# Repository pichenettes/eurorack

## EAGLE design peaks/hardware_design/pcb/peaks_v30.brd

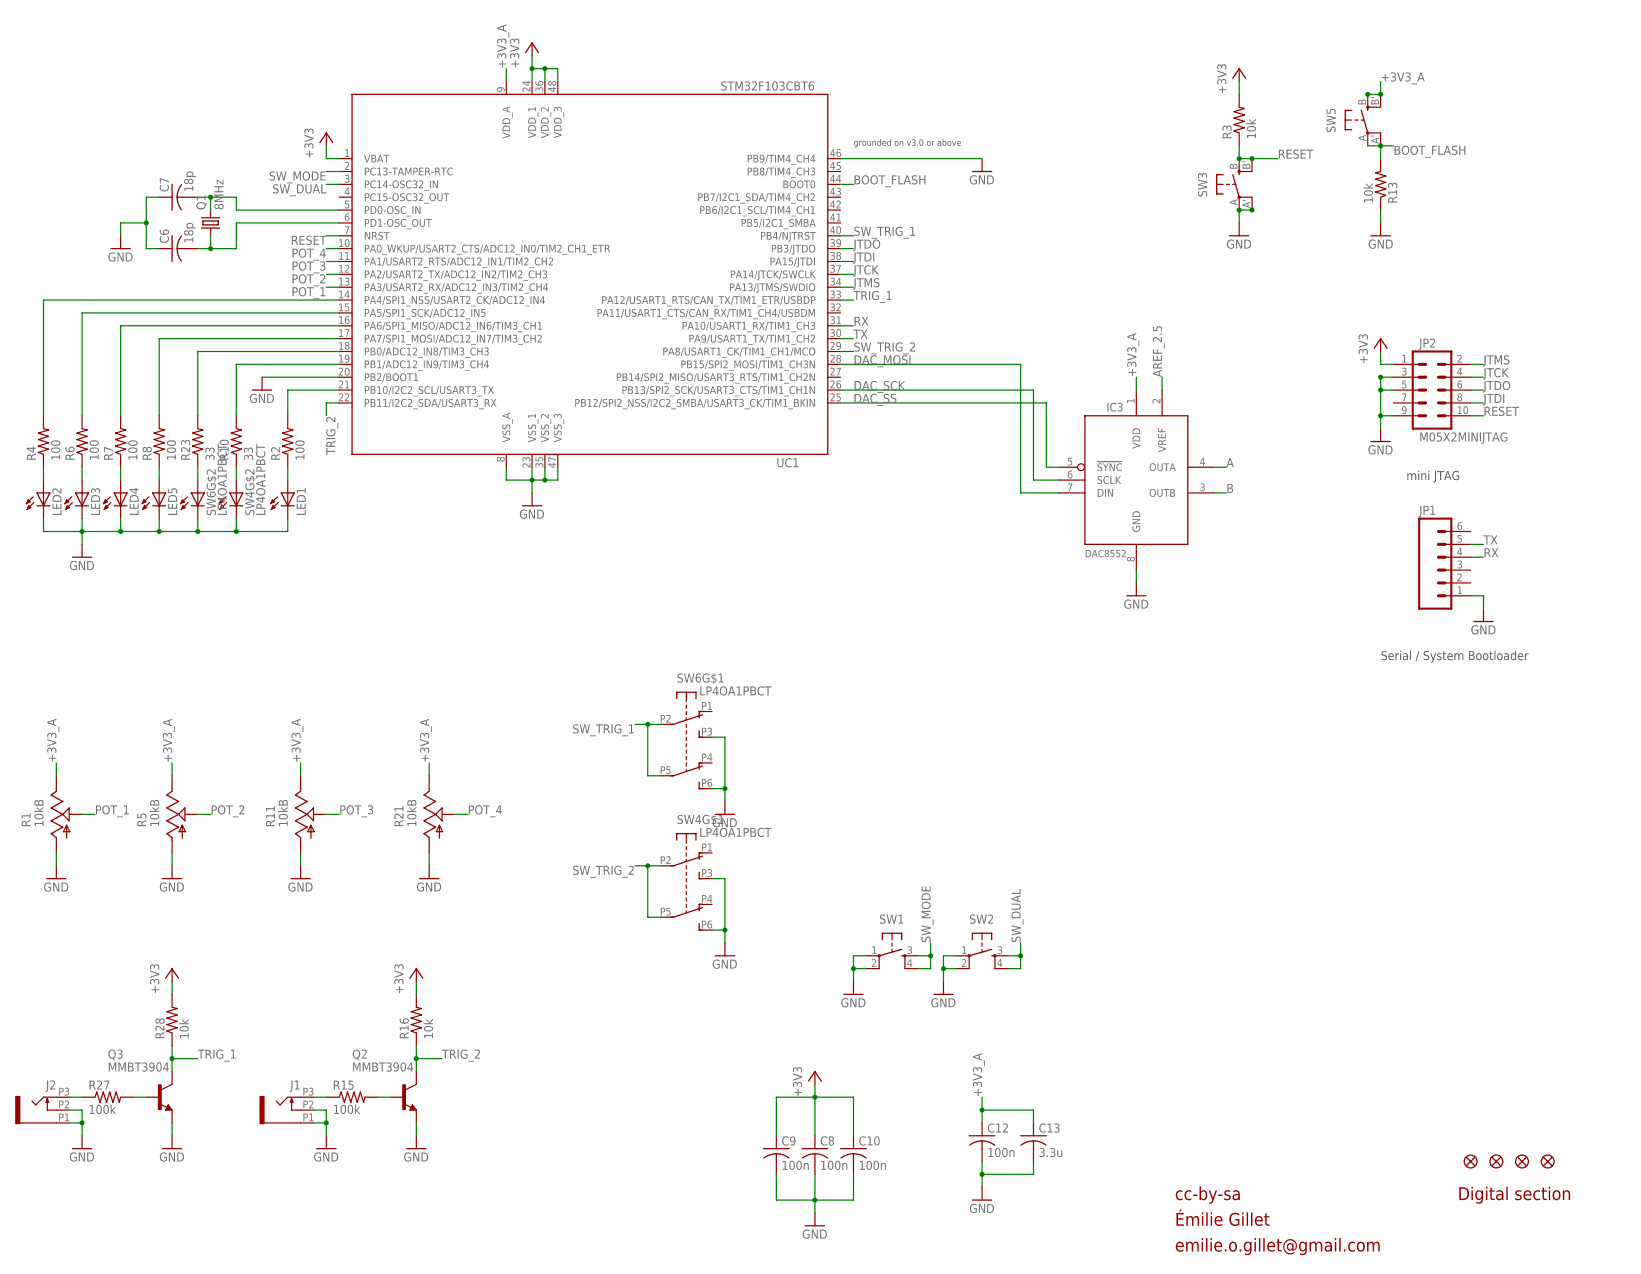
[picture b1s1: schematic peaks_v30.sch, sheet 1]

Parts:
C6, C7: 18p; C0603
C8, C9, C10, C12: 100n; C0603
C13: 3.3u; C0603
F1, F2, F3, F4: FIDUCIAL1X2; FIDUCIAL-1X2
IC3: DAC8552; MSOP-8
J1, J2: PJ301_THONKICONN6; WQP_PJ_301M6
JP1: M06SIP; 1X06
JP2: M05X2MINIJTAG; 2X5-1.27
LED1, LED2, LED3, LED4, LED5: LED3MM
Q1: 8MHz; HC49UP
Q2, Q3: MMBT3904; SOT23-BEC
R1, R5, R11, R21: 10kB; ALPS_POT_VERTICAL_PS
R2, R4, R6, R7, R8: 100; R0603
R3, R13, R16, R28: 10k; R0603
R10, R23: 33; R0603
R15, R27: 100k; R0603
SW1, SW2: TAC_SWITCHPTH; TACTILE-PTH
SW3, SW5: EVQQ2; EVQ-Q2
SW4, SW6: LP4OA1PBCT
UC1: STM32F103CBT6; LQFP48

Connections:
+3V3: C8.1, C9.1, C10.1, JP2.1, R3.2, R16.2, R28.2, UC1.1 (VBAT), UC1.24 (VDD_1), UC1.36 (VDD_2), UC1.48 (VDD_3); also elsewhere on the board
+3V3_A: C12.1, C13.1, IC3.1 (VDD), R1.P$1 (E), R5.P$1 (E), R11.P$1 (E), R21.P$1 (E), SW5.B (S), SW5.B' (S1), UC1.9 (VDD_A); also elsewhere on the board
A: IC3.4 (OUTA); also elsewhere on the board
AREF_2.5: IC3.2 (VREF); also elsewhere on the board
B: IC3.3 (OUTB); also elsewhere on the board
BOOT_FLASH: R13.2, SW5.A, SW5.A' (P1), UC1.44 (BOOT0)
DAC_MOSI: IC3.7 (DIN), UC1.28 (PB15/SPI2_MOSI/TIM1_CH3N)
DAC_SCK: IC3.6 (SCLK), UC1.26 (PB13/SPI2_SCK/USART3_CTS/TIM1_CH1N)
DAC_SS: IC3.5 (!SYNC), UC1.25 (PB12/SPI2_NSS/I2C2_SMBA/USART3_CK/TIM1_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)
GND: C6.1, C7.1, C8.2, C9.2, C10.2, C12.2, C13.2, IC3.8 (GND), J1.P1 (1), J1.P2 (2), J2.P1 (1), J2.P2 (2), JP1.1, JP2.3, JP2.5, JP2.9, LED1.K (C), LED2.K (C), LED3.K (C), LED4.K (C), LED5.K (C), Q2.E, Q3.E, R1.P$3 (A), R5.P$3 (A), R11.P$3 (A), R13.1, R21.P$3 (A), SW1.1, SW1.2, SW2.1, SW2.2, SW3.A, SW3.A' (P1), SW4.L2, SW4.P3 (A3), SW4.P6 (B3), SW6.L2, SW6.P3 (A3), SW6.P6 (B3), UC1.8 (VSS_A), UC1.20 (PB2/BOOT1), UC1.23 (VSS_1), UC1.35 (VSS_2), UC1.46 (PB9/TIM4_CH4), UC1.47 (VSS_3); also elsewhere on the board
JTCK: JP2.4, UC1.37 (PA14/JTCK/SWCLK)
JTDI: JP2.8, UC1.38 (PA15/JTDI)
JTDO: JP2.6, UC1.39 (PB3/JTDO)
JTMS: JP2.2, UC1.34 (PA13/JTMS/SWDIO)
unnamed: J1.P3 (3), R15.1
unnamed: R23.2, UC1.18 (PB0/ADC12_IN8/TIM3_CH3)
unnamed: LED2.A, R4.1
unnamed: LED3.A, R6.1
unnamed: LED4.A, R7.1
unnamed: LED5.A, R8.1
unnamed: C7.2, Q1.2, UC1.5 (PD0-OSC_IN)
unnamed: C6.2, Q1.1, UC1.6 (PD1-OSC_OUT)
unnamed: R10.2, UC1.19 (PB1/ADC12_IN9/TIM3_CH4)
unnamed: R4.2, UC1.14 (PA4/SPI1_NSS/USART2_CK/ADC12_IN4)
unnamed: R6.2, UC1.15 (PA5/SPI1_SCK/ADC12_IN5)
unnamed: R7.2, UC1.16 (PA6/SPI1_MISO/ADC12_IN6/TIM3_CH1)
unnamed: R8.2, UC1.17 (PA7/SPI1_MOSI/ADC12_IN7/TIM3_CH2)
unnamed: Q2.B, R15.2
unnamed: R23.1, SW6.L1
unnamed: R10.1, SW4.L1
unnamed: LED1.A, R2.1
unnamed: R2.2, UC1.21 (PB10/I2C2_SCL/USART3_TX)
unnamed: J2.P3 (3), R27.1
unnamed: Q3.B, R27.2
POT_1: R1.P$2 (S), UC1.13 (PA3/USART2_RX/ADC12_IN3/TIM2_CH4)
POT_2: R5.P$2 (S), UC1.12 (PA2/USART2_TX/ADC12_IN2/TIM2_CH3)
POT_3: R11.P$2 (S), UC1.11 (PA1/USART2_RTS/ADC12_IN1/TIM2_CH2)
POT_4: R21.P$2 (S), UC1.10 (PA0_WKUP/USART2_CTS/ADC12_IN0/TIM2_CH1_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)
RESET: JP2.10, R3.1, SW3.B (S), SW3.B' (S1), UC1.7 (NRST)
RX: JP1.4, UC1.31 (PA10/USART1_RX/TIM1_CH3)
SW_DUAL: SW2.3, SW2.4, UC1.3 (PC14-OSC32_IN)
SW_MODE: SW1.3, SW1.4, UC1.2 (PC13-TAMPER-RTC)
SW_TRIG_1: SW6.P2 (A2), SW6.P5 (B2), UC1.40 (PB4/NJTRST)
SW_TRIG_2: SW4.P2 (A2), SW4.P5 (B2), UC1.29 (PA8/USART1_CK/TIM1_CH1/MCO)
TRIG_1: Q3.C, R28.1, UC1.33 (PA12/USART1_RTS/CAN_TX/TIM1_ETR/USBDP)
TRIG_2: Q2.C, R16.1, UC1.22 (PB11/I2C2_SDA/USART3_RX)
TX: JP1.5, UC1.30 (PA9/USART1_TX/TIM1_CH2)

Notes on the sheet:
cc-by-sa
Digital section
mini JTAG
Serial / System Bootloader
grounded on v3.0 or above
Émilie Gillet
emilie.o.gillet@gmail.com

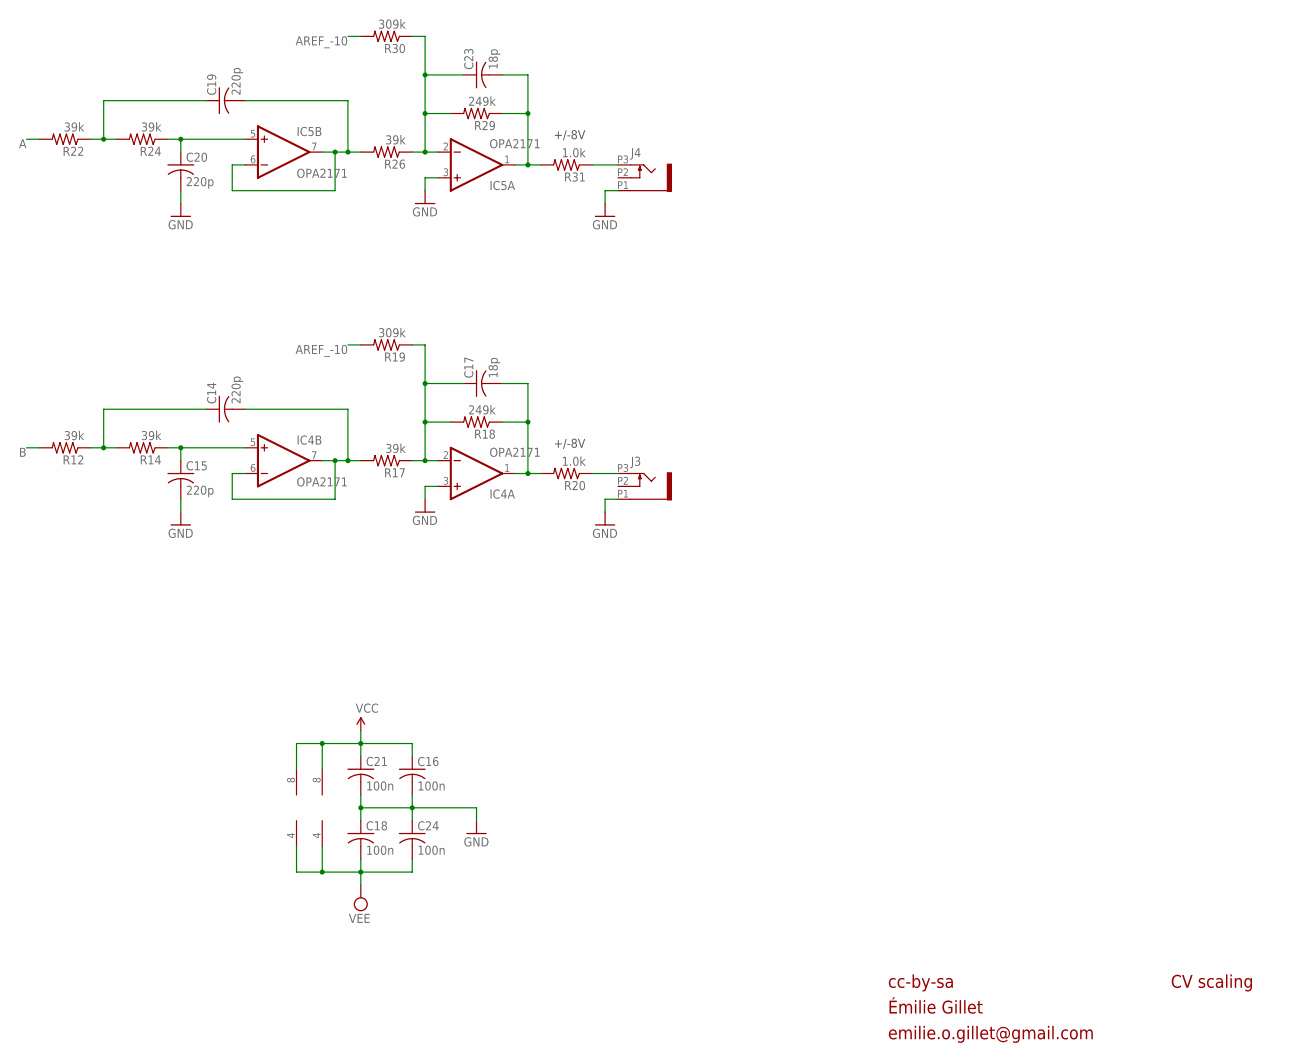
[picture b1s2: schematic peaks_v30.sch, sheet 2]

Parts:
C14, C15, C19, C20: 220p; C0603
C16, C18, C21, C24: 100n; C0603
C17, C23: 18p; C0603
IC4, IC5: OPA2171; SO08
J3, J4: PJ301_THONKICONN6; WQP_PJ_301M6
R12, R14, R17, R22, R24, R26: 39k; R0603
R18, R29: 249k; R0603
R19, R30: 309k; R0603
R20, R31: 1.0k; R0603

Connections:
A: R22.2; also elsewhere on the board
AREF_-10: R19.2, R30.2; also elsewhere on the board
B: R12.2; also elsewhere on the board
BI_OUT: C17.2, IC4.1 (OUT), R18.1, R20.2
BI_OUT1: C23.2, IC5.1 (OUT), R29.1, R31.2
F_CV: C17.1, IC4.2 (-IN), R17.1, R18.2, R19.1
F_CV1: C23.1, IC5.2 (-IN), R26.1, R29.2, R30.1
GND: C15.2, C16.2, C18.1, C20.2, C21.2, C24.1, IC4.3 (+IN), IC5.3 (+IN), J3.P1 (1), J4.P1 (1); also elsewhere on the board
unnamed: C19.2, IC5.6 (-IN), IC5.7 (OUT), R26.2
unnamed: C20.1, IC5.5 (+IN), R24.1
unnamed: C19.1, R22.1, R24.2
unnamed: J3.P3 (3), R20.1
unnamed: J4.P3 (3), R31.1
unnamed: C14.2, IC4.6 (-IN), IC4.7 (OUT), R17.2
unnamed: C15.1, IC4.5 (+IN), R14.1
unnamed: C14.1, R12.1, R14.2
VCC: C16.1, C21.1, IC4.8 (V+), IC5.8 (V+); also elsewhere on the board
VEE: C18.2, C24.2, IC4.4 (V-), IC5.4 (V-); also elsewhere on the board

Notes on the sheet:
+/-8V
cc-by-sa
CV scaling
Émilie Gillet
emilie.o.gillet@gmail.com

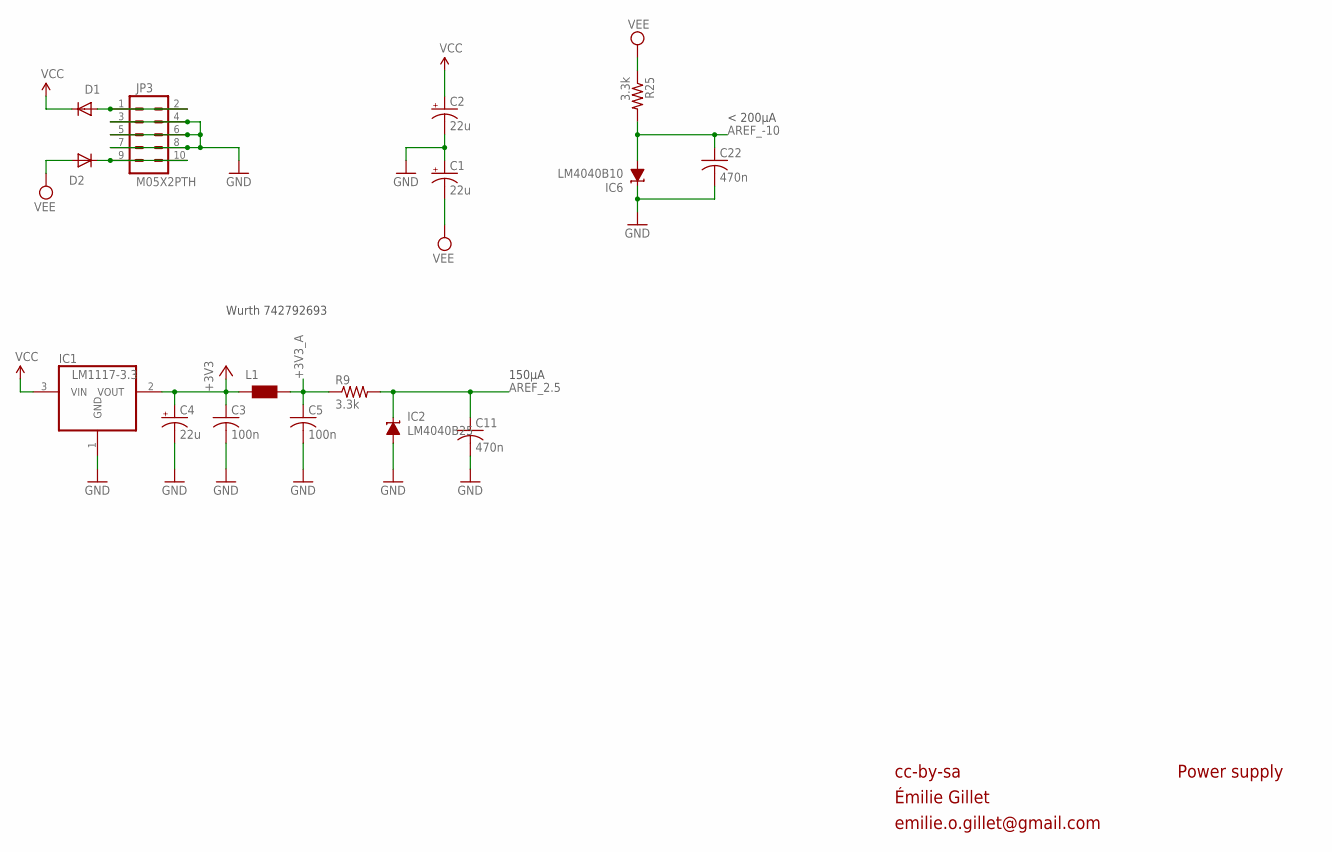
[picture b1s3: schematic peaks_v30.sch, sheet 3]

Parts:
C1, C2, C4: 22u; PANASONIC_C
C3, C5: 100n; C0603
C11, C22: 470n; C0603
D1, D2: 1N5819HW; SOD123
IC1: LM1117-3.3; SOT223
IC2: LM4040B25; DBZ_R-PDSO-G3
IC6: LM4040B10; DBZ_R-PDSO-G3
JP3: M05X2PTH; AVR_ICSP
L1: WE-CBF_0603; 0603
R9, R25: 3.3k; R0603

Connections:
+3V3: C3.1, C4.+, IC1.2 (VOUT), L1.1; also elsewhere on the board
+3V3_A: C5.1, L1.2, R9.1; also elsewhere on the board
AREF_2.5: C11.1, IC2.1 (C), R9.2; also elsewhere on the board
AREF_-10: C22.1, IC6.2 (A), R25.2; also elsewhere on the board
GND: C1.+, C2.-, C3.2, C4.-, C5.2, C11.2, C22.2, IC1.1 (GND), IC2.2 (A), IC6.1 (C), JP3.3, JP3.4, JP3.5, JP3.6, JP3.7, JP3.8; also elsewhere on the board
unnamed: D1.A, JP3.1, JP3.2
unnamed: D2.C, JP3.9, JP3.10
VCC: C2.+, D1.C, IC1.3 (VIN); also elsewhere on the board
VEE: C1.-, D2.A, R25.1; also elsewhere on the board

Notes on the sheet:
cc-by-sa
Power supply
Wurth 742792693
< 200µA
150µA
Émilie Gillet
emilie.o.gillet@gmail.com

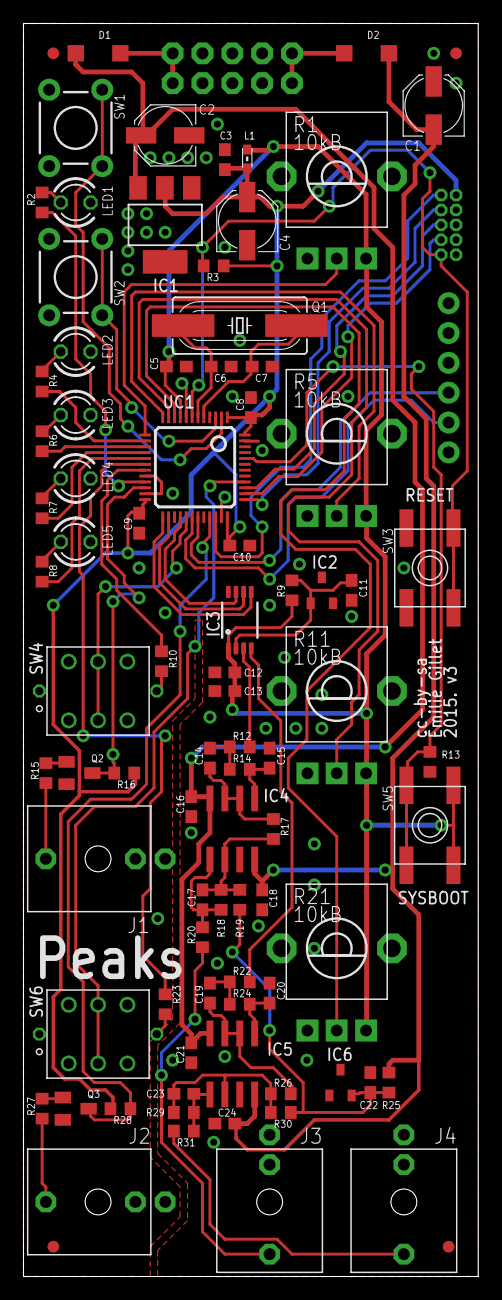
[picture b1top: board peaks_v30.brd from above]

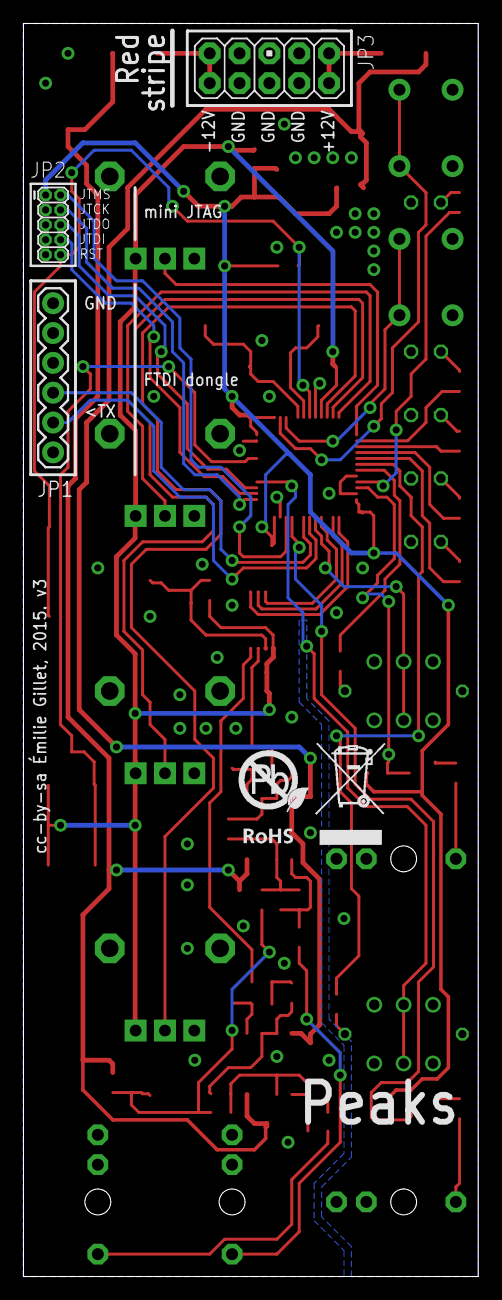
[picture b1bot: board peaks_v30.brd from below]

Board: 2 copper layers, 38.7 x 106.7 mm, 91 parts (4 on the bottom side), 64 nets.

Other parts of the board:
U$2: ROHS

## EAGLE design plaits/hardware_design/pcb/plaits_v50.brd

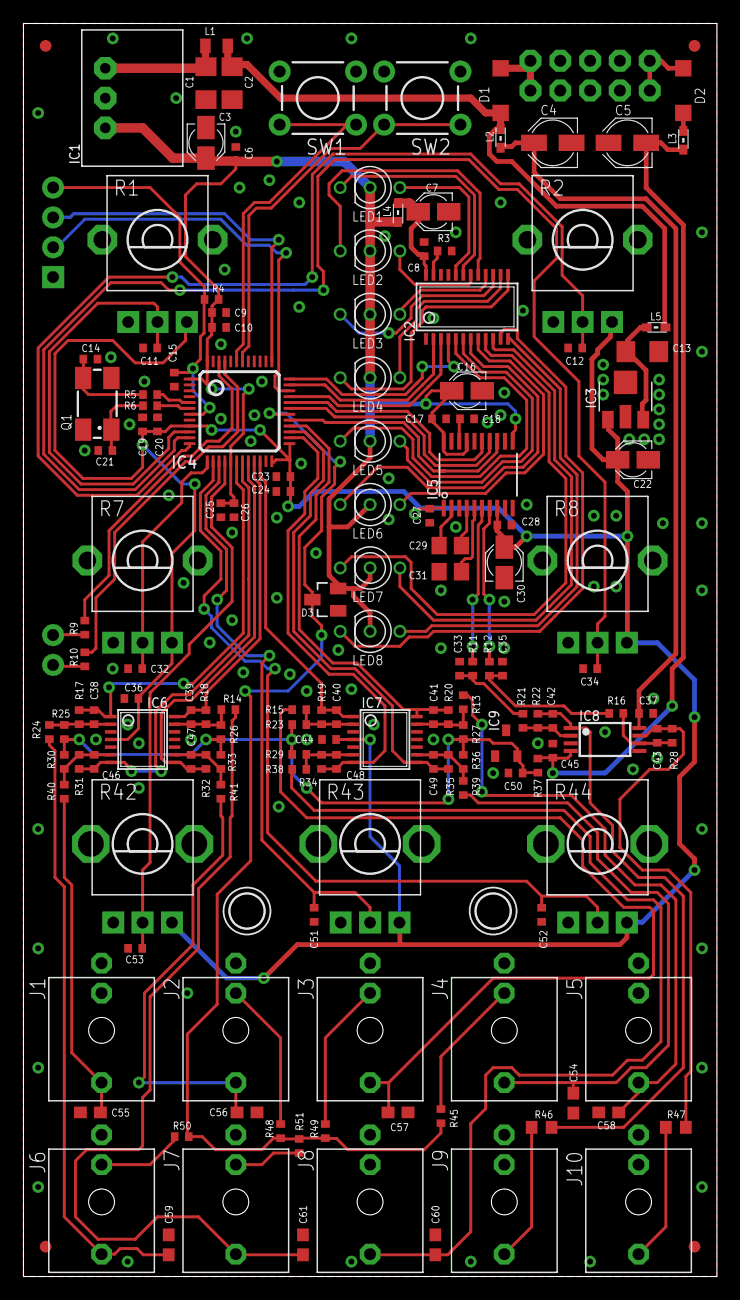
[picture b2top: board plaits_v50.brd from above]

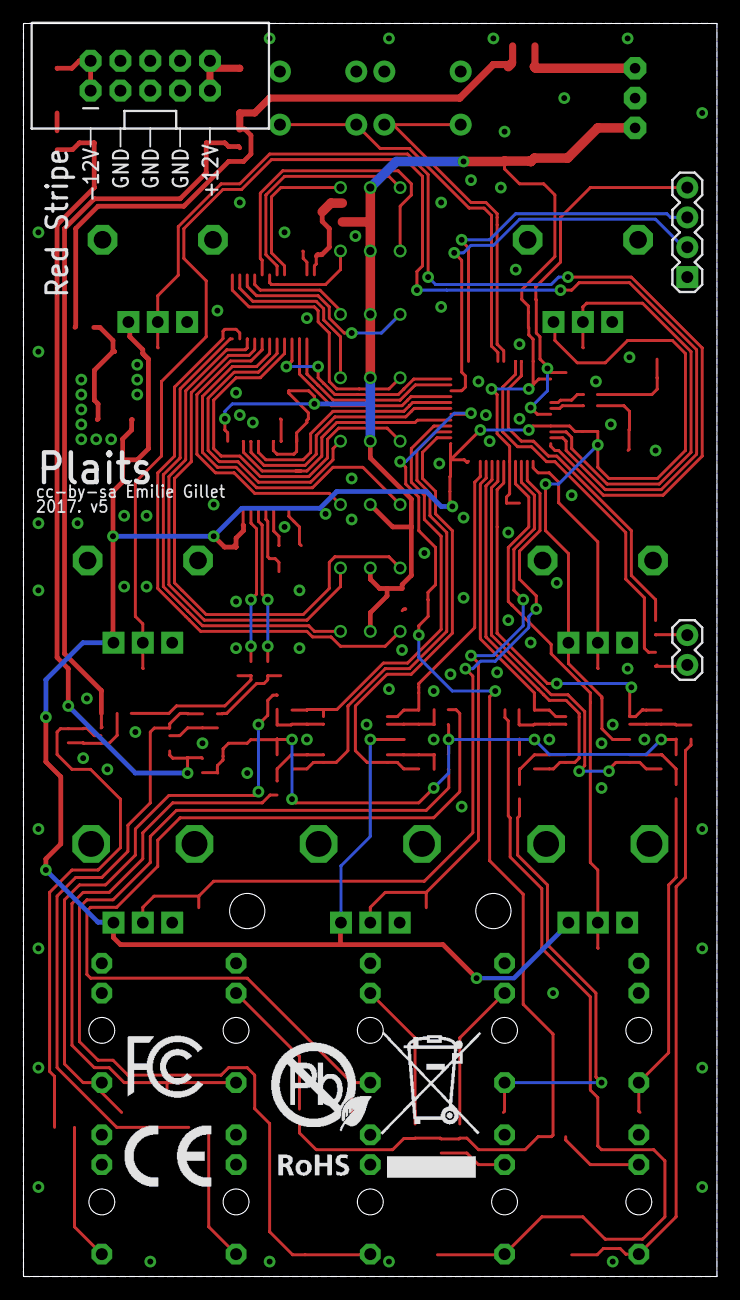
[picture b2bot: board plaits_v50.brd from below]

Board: 2 copper layers, 59.0 x 106.7 mm, 162 parts (6 on the bottom side), 100 nets.

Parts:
C1, C2, C13: 22u; C1206
C3, C7, C16, C22, C30: 10u; PANASONIC_A
C4, C5: 22u; PANASONIC_B
C6, C8, C10, C11, C12, C15, C17, C18, C20, C23, C26, C27, C28, C32, C34, C36, C37, C44, C45, C51, C52, C53: 100n; C0402
C9, C19, C24, C25, C50: 1u; C0402
C14, C21: 20p; C0402
C29, C31: 2.2u; C0805
C33, C35, C39, C40, C41, C47, C48, C49: 1.0n; C0402
C38, C42, C43, C46: 100p; C0402
C54, C55, C56, C57, C58, C59, C60, C61: ESD; C0603
D1, D2: 1N5819HW; SOD123
D3: BAT54S; SOT23
H2, H3: MOUNT-HOLE; 3,0TINY
IC1: R-78E3.3-0.5; WE78
IC2: TLC59281DBQ; TSSOP24_0635
IC3: LD2981ABU33; SOT89
IC4: STM32F373CCT6; LQFP48
IC5: PCM5100APW; SSOP20
IC6, IC7: MCP6004; TSSOP14_065
IC8: TL072PW; TSSOP08
IC9: LM4040B10; DBZ_R-PDSO-G3
J1, J2, J3, J4, J5, J6, J7, J8, J9, J10: PJ301_THONKICONN6; WQP_PJ_301M6
JP1, JP2, JP3, JP4: FIDUCIAL1X2; FIDUCIAL-1X2
JP5: 1X02
JP6: 1X04
JP8: M05X2SHD; 2X5-SHROUDED
L1: 33u; L2012C
L2, L3, L4, L5: 0603
LED1, LED2, LED3, LED4, LED5, LED6, LED7, LED8: SSL-LX3059IGW-CA; LED-BICOLOR-THROUGHHOLE-LUMEX
Q1: 8MHz; CTS406
R1, R2, R7, R8: 10kB; ALPS_POT_VERTICAL_PS
R3, R4, R16, R21, R45, R48, R49, R50, R51: 10k; R0402
R5, R6, R9, R10: 100; R0402
R11, R12, R37: 2.2k; R0402
R13, R14, R15, R24, R38, R39, R40, R41: 100k; R0402
R17: 56k; R0402
R18, R20, R22, R28, R31, R34: 33k; R0402
R19, R32, R35: 20k; R0402
R23, R33, R36: 120k; R0402
R25, R27, R30: 200k; R0402
R26: 110k; R0402
R29: 140k; R0402
R42, R43, R44: 10kB; ALPS_POT_VERTICAL
R46, R47: 1.0k; R0603
SW1, SW2: TACTILE-PTH
U$1: FCC_MEDIUM
U$2: ROHS_BIG
U$3: CE_MEDIUM

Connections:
+3V3: C3.+, C6.1, C9.1, C10.1, C16.+, C17.1, C25.1, C26.1, D3.2, IC1.3, IC4.1, IC4.17, IC4.48, IC5.11, IC5.17, IC5.20, L4.2, LED1.A, LED2.A, LED3.A, LED4.A, LED5.A, LED6.A, LED7.A, LED8.A, R4.1
+3V3_A: C19.1, C20.1, C22.+, C23.1, C24.1, C27.1, C28.1, C30.+, C36.1, C44.1, IC3.1, IC4.9, IC4.24, IC4.25, IC5.1, IC5.8, IC6.4, IC7.4, R1.P$1, R2.P$1, R7.P$1, R8.P$1, R42.P$1, R43.P$1, R44.P$1
ADC_FM: C40.2, IC4.22, IC7.1, R19.1
ADC_GATE: C39.2, IC4.21, IC6.14, R18.1
ADC_HARMONICS: C41.2, IC4.28, IC7.14, R20.1
ADC_MODEL: C46.2, IC4.19, IC6.7, R31.1
ADC_MORPH: C49.2, IC4.27, IC7.8, R35.1
ADC_TIMBRE: C47.2, IC4.20, IC6.8, R32.1
ADC_TRIG: C38.2, IC4.18, IC6.1, R17.1
ADC_V_OCT: C48.2, IC4.26, IC7.7, R34.1
AREF_-10: C50.1, IC9.2, R23.2, R25.2, R26.2, R27.2, R29.2, R30.2, R33.2, R36.2, R37.2
DAC_BCK: IC4.29, IC5.13
DAC_DIN: IC4.31, IC5.14
DAC_LRCK: IC4.32, IC5.15
FM_IN: C57.1, J3.P3, R15.2
FREQ_ATT: C51.1, IC4.15, R43.P$2
FREQ_POT: C11.1, IC4.10, R1.P$2
GATE_IN: C61.1, J7.P3, R14.2
GATE_IN1: C59.1, J6.P3, R24.2
GND: C1.2, C2.2, C3.-, C4.-, C5.+, C6.2, C7.-, C8.2, C9.2, C10.2, C11.2, C12.2, C13.2, C14.1, C15.2, C16.-, C17.2, C18.2, C19.2, C20.2, C21.1, C22.-, C23.2, C24.2, C25.2, C26.2, C27.2, C28.2, C30.-, C31.2, C32.2, C33.2, C34.2, C35.2, C36.2, C37.2, C44.2, C45.1, C50.2, C51.2, C52.2, C53.2, C54.2, C55.2, C56.2, C57.2, C58.2, C59.2, C60.2, C61.2, D3.1, IC1.2, IC2.1, IC2.21, IC3.2, IC4.8, IC4.23, IC4.44, IC4.47, IC5.3, IC5.9, IC5.10, IC5.12, IC5.16, IC5.19, IC6.3, IC6.5, IC6.10, IC6.11, IC6.12, IC7.3, IC7.5, IC7.10, IC7.11, IC7.12, IC8.3, IC8.5, IC9.1, J1.P1, J1.P2, J2.P1, J3.P1, J4.P1, J5.P1, J5.P2, J6.P1, J7.P1, J8.P1, J8.P2, J9.P1, J10.P1, JP6.1, JP8.3, JP8.4, JP8.5, JP8.6, JP8.7, JP8.8, Q1.2, Q1.4, R1.P$3, R2.P$3, R3.2, R7.P$3, R8.P$3, R42.P$3, R43.P$3, R44.P$3, SW1.1, SW1.2, SW2.1, SW2.2
HARMONICS_IN: C58.1, J5.P3, R13.2
HARMONICS_POT: C12.1, IC4.12, R2.P$2
LEDS_SCK: IC2.3, IC4.33
LEDS_SIN: IC2.2, IC4.35
LEDS_SS: IC2.4, IC4.36
MODEL_IN: C55.1, J1.P3, R40.2
MORPH_ATT: C52.1, IC4.14, R44.P$2
MORPH_IN: C54.1, J4.P3, R39.2
MORPH_POT: C34.1, IC4.11, R8.P$2
unnamed: C1.1, IC1.1, L1.2
unnamed: IC2.12, LED8.GREEN_C
unnamed: J6.P2, R50.2
unnamed: C38.1, IC6.2, R17.2, R24.1, R25.1
unnamed: IC2.11, LED8.RED_C
unnamed: C29.1, IC5.2
unnamed: IC4.5, R5.1
unnamed: IC4.6, R6.1
unnamed: IC2.10, LED7.GREEN_C
unnamed: IC2.9, LED7.RED_C
unnamed: IC2.8, LED6.GREEN_C
unnamed: IC2.13, LED4.RED_C
unnamed: IC2.7, LED6.RED_C
unnamed: IC2.14, LED4.GREEN_C
unnamed: IC2.6, LED5.GREEN_C
unnamed: C29.2, IC5.4
unnamed: IC2.15, LED3.RED_C
unnamed: IC2.16, LED3.GREEN_C
unnamed: IC2.17, LED2.RED_C
unnamed: IC2.18, LED2.GREEN_C
unnamed: IC2.19, LED1.RED_C
unnamed: IC2.5, LED5.RED_C
unnamed: IC2.20, LED1.GREEN_C
unnamed: J3.P2, R49.1
unnamed: J2.P2, R48.1
unnamed: J4.P2, R45.1
unnamed: C7.+, C8.1, IC2.24, L4.1
unnamed: C39.1, IC6.13, R14.1, R18.2, R26.1
unnamed: C14.2, Q1.3, R5.2
unnamed: C48.1, IC7.6, R29.1, R34.2, R38.1
unnamed: C56.1, J2.P3, R41.2
unnamed: C49.1, IC7.9, R35.2, R36.1, R39.1
unnamed: JP5.2, R10.1
unnamed: C40.1, IC7.2, R15.1, R19.2, R23.1
unnamed: C21.2, Q1.1, R6.2
unnamed: J7.P2, R51.1
unnamed: C46.1, IC6.6, R30.1, R31.2, R40.1
unnamed: D2.A, L3.2
unnamed: C47.1, IC6.9, R32.2, R33.1, R41.1
unnamed: C2.1, D1.C, L1.1, L2.2, L5.2
unnamed: C41.1, IC7.13, R13.1, R20.2, R27.1
unnamed: C13.1, IC3.3, L5.1
unnamed: IC5.6, R11.2
unnamed: C33.1, R11.1, R21.2
unnamed: C35.1, R12.1, R16.2
unnamed: C31.1, IC5.5
unnamed: JP5.1, R9.1
unnamed: C18.1, IC5.18
unnamed: IC5.7, R12.2
unnamed: D1.A, JP8.9, JP8.10
unnamed: C43.1, IC8.6, R16.1, R28.2
unnamed: C43.2, IC8.7, R28.1, R47.2
unnamed: C42.1, IC8.2, R21.1, R22.2
unnamed: C42.2, IC8.1, R22.1, R46.2
unnamed: D2.C, JP8.1, JP8.2
unnamed: J9.P3, R46.1
unnamed: IC2.23, R3.1
unnamed: J10.P3, R47.1
NORMALIZATION_PROBE: D3.3, IC4.30, R45.2, R48.2, R49.2, R50.1, R51.2
RESET: C15.1, IC4.7, JP6.4, R4.2
RX: IC4.46, R9.2
SWCLK: IC4.37, JP6.3
SWDIO: IC4.34, JP6.2
SW_1: IC4.43, SW1.3, SW1.4
SW_2: IC4.42, SW2.3, SW2.4
TIMBRE_ATT: C53.1, IC4.16, R42.P$2
TIMBRE_POT: C32.1, IC4.13, R7.P$2
TX: IC4.45, R10.2
VCC: C4.+, C37.1, IC8.8, L2.1
VEE: C5.-, C45.2, IC8.4, L3.1, R37.1
V_OCT_IN: C60.1, J8.P3, R38.2

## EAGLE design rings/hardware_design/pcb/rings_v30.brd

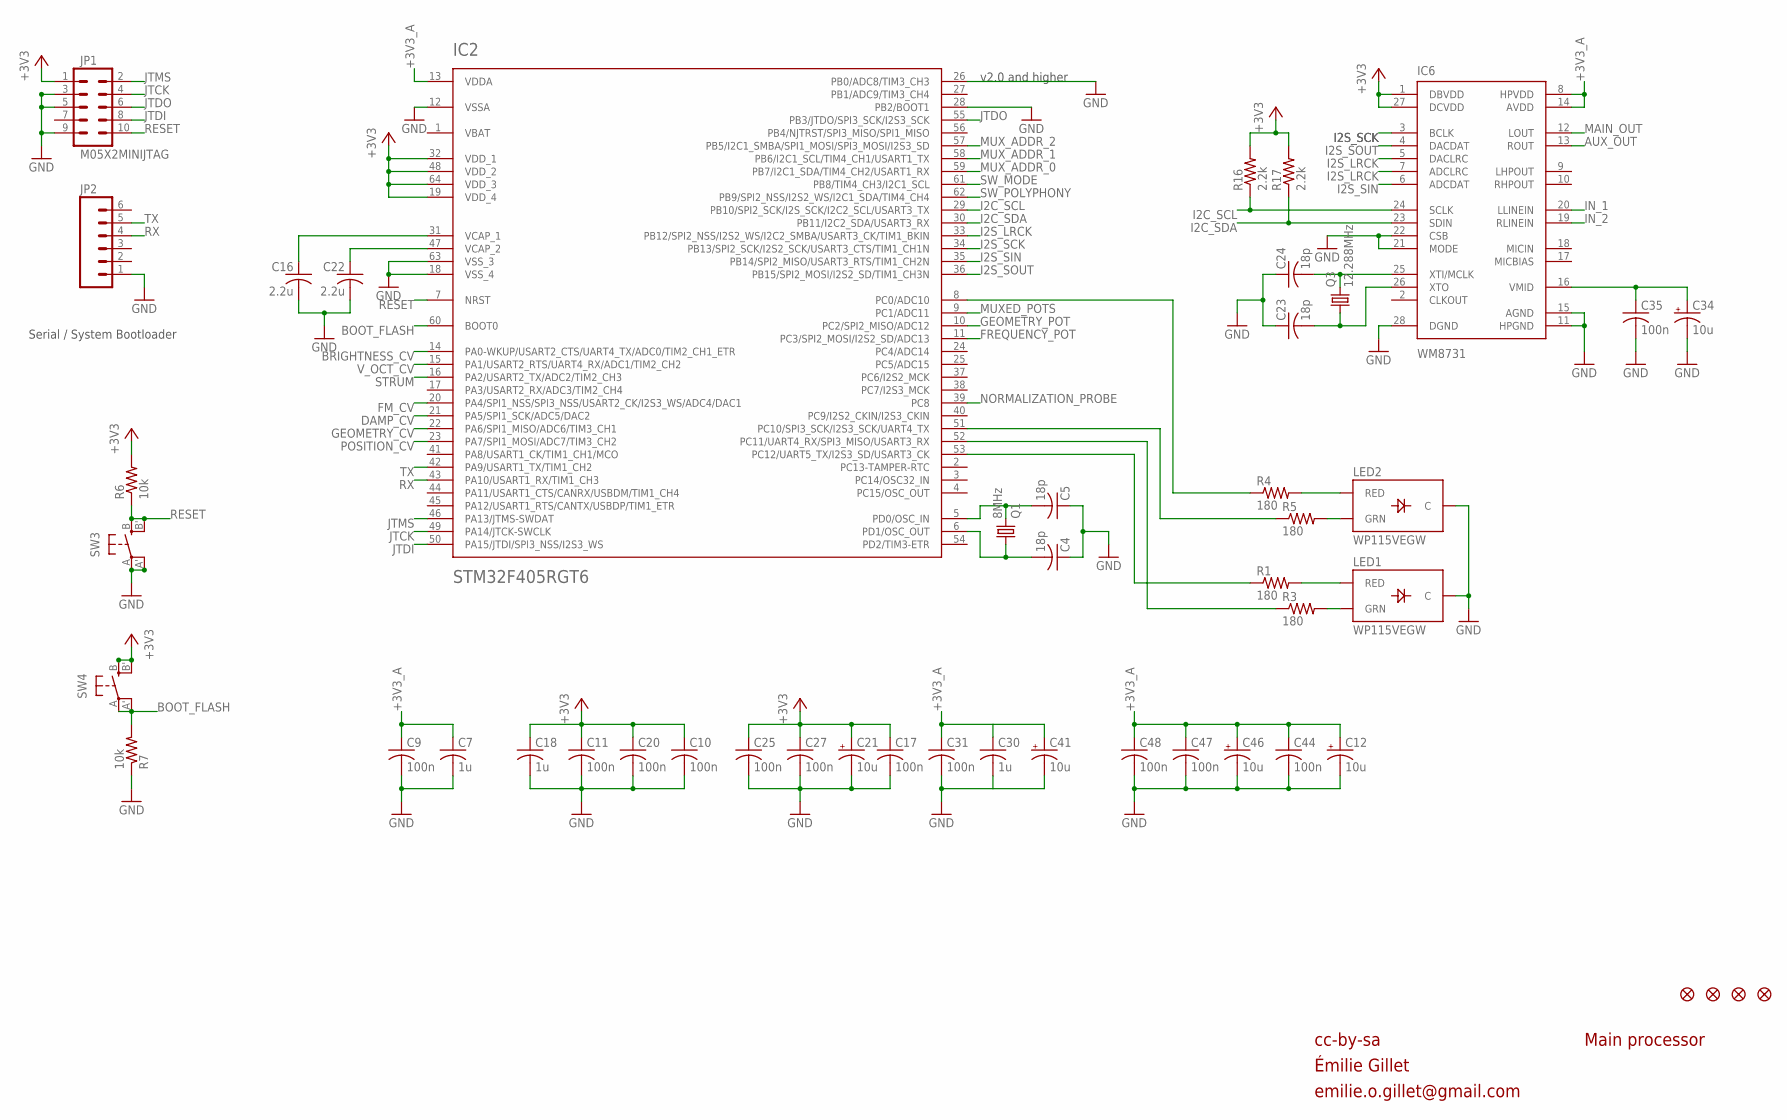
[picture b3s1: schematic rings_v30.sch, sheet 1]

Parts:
C4, C5, C23, C24: 18p; C0603
C7, C18, C30: 1u; C0603
C9, C10, C11, C17, C20, C25, C27, C31, C35, C44, C47, C48: 100n; C0603
C12, C21, C34, C41, C46: 10u; PANASONIC_A
C16, C22: 2.2u; C0805
F1, F2, F3, F4: FIDUCIAL1X2; FIDUCIAL-1X2
IC2: STM32F405RGT6; TQFP-10X10-64
IC6: WM8731; SSOP28
JP1: M05X2MINIJTAG; 2X5-1.27
JP2: M06SIP; 1X06
LED1, LED2: WP115VEGW; LED-BICOLOR-THROUGHHOLE
Q1: 8MHz; HC49UP
Q3: 12.288MHz; HC49UP
R1, R3, R4, R5: 180; R0603
R6, R7: 10k; R0603
R16, R17: 2.2k; R0603
SW3, SW4: EVQQ2; EVQ-Q2

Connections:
+3V3: C10.1, C11.1, C17.1, C18.1, C20.1, C21.+, C25.1, C27.1, IC2.19 (VDD_4), IC2.32 (VDD_1), IC2.48 (VDD_2), IC2.64 (VDD_3), IC6.1 (DBVDD), IC6.27 (DCVDD), JP1.1, R6.2, R16.2, R17.2, SW4.B (S), SW4.B' (S1); also elsewhere on the board
+3V3_A: C7.1, C9.1, C12.+, C30.1, C31.1, C41.+, C44.1, C46.+, C47.1, C48.1, IC2.13 (VDDA), IC6.8 (HPVDD), IC6.14 (AVDD); also elsewhere on the board
AUX_OUT: IC6.13 (ROUT); also elsewhere on the board
BOOT_FLASH: IC2.60 (BOOT0), R7.2, SW4.A, SW4.A' (P1)
BRIGHTNESS_CV: IC2.14 (PA0-WKUP/USART2_CTS/UART4_TX/ADC0/TIM2_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); also elsewhere on the board
DAMP_CV: IC2.21 (PA5/SPI1_SCK/ADC5/DAC2); also elsewhere on the board
FM_CV: IC2.20 (PA4/SPI1_NSS/SPI3_NSS/USART2_CK/I2S3_WS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); also elsewhere on the board
FREQUENCY_POT: IC2.11 (PC3/SPI2_MOSI/I2S2_SD/ADC13); also elsewhere on the board
GEOMETRY_CV: IC2.22 (PA6/SPI1_MISO/ADC6/TIM3_CH1); also elsewhere on the board
GEOMETRY_POT: IC2.10 (PC2/SPI2_MISO/ADC12); also elsewhere on the board
GND: C4.1, C5.1, C7.2, C9.2, C10.2, C11.2, C12.-, C16.2, C17.2, C18.2, C20.2, C21.-, C22.2, C23.1, C24.1, C25.2, C27.2, C30.2, C31.2, C34.-, C35.2, C41.-, C44.2, C46.-, C47.2, C48.2, IC2.12 (VSSA), IC2.18 (VSS_4), IC2.26 (PB0/ADC8/TIM3_CH3), IC2.28 (PB2/BOOT1), IC2.63 (VSS_3), IC6.11 (HPGND), IC6.15 (AGND), IC6.21 (MODE), IC6.22 (CSB), IC6.28 (DGND), JP1.3, JP1.5, JP1.9, JP2.1, LED1.2 (C), LED2.2 (C), R7.1, SW3.A, SW3.A' (P1); also elsewhere on the board
I2C_SCL: IC2.29 (PB10/SPI2_SCK/I2S_SCK/I2C2_SCL/USART3_TX), IC6.24 (SCLK), R16.1
I2C_SDA: IC2.30 (PB11/I2C2_SDA/USART3_RX), IC6.23 (SDIN), R17.1
I2S_LRCK: IC2.33 (PB12/SPI2_NSS/I2S2_WS/I2C2_SMBA/USART3_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), IC6.5 (DACLRC), IC6.7 (ADCLRC)
I2S_SCK: IC2.34 (PB13/SPI2_SCK/I2S2_SCK/USART3_CTS/TIM1_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), IC6.3 (BCLK)
I2S_SIN: IC2.35 (PB14/SPI2_MISO/USART3_RTS/TIM1_CH2N), IC6.6 (ADCDAT)
I2S_SOUT: IC2.36 (PB15/SPI2_MOSI/I2S2_SD/TIM1_CH3N), IC6.4 (DACDAT)
IN_1: IC6.20 (LLINEIN); also elsewhere on the board
IN_2: IC6.19 (RLINEIN); also elsewhere on the board
JTCK: IC2.49 (PA14/JTCK-SWCLK), JP1.4
JTDI: IC2.50 (PA15/JTDI/SPI3_NSS/I2S3_WS), JP1.8
JTDO: IC2.55 (PB3/JTDO/SPI3_SCK/I2S3_SCK), JP1.6
JTMS: IC2.46 (PA13/JTMS-SWDAT), JP1.2
MAIN_OUT: IC6.12 (LOUT); also elsewhere on the board
MUXED_POTS: IC2.9 (PC1/ADC11); also elsewhere on the board
MUX_ADDR_0: IC2.59 (PB7/I2C1_SDA/TIM4_CH2/USART1_RX); also elsewhere on the board
MUX_ADDR_1: IC2.58 (PB6/I2C1_SCL/TIM4_CH1/USART1_TX); also elsewhere on the board
MUX_ADDR_2: IC2.57 (PB5/I2C1_SMBA/SPI1_MOSI/SPI3_MOSI/I2S3_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); also elsewhere on the board
unnamed: C5.2, IC2.5 (PD0/OSC_IN), Q1.2
unnamed: C4.2, IC2.6 (PD1/OSC_OUT), Q1.1
unnamed: LED1.3 (RED), R1.2
unnamed: C22.1, IC2.47 (VCAP_2)
unnamed: C34.+, C35.1, IC6.16 (VMID)
unnamed: C16.1, IC2.31 (VCAP_1)
unnamed: LED1.1 (GRN), R3.2
unnamed: LED2.3 (RED), R4.2
unnamed: LED2.1 (GRN), R5.2
unnamed: IC2.52 (PC11/UART4_RX/SPI3_MISO/USART3_RX), R3.1
unnamed: IC2.8 (PC0/ADC10), R4.1
unnamed: C24.2, IC6.25 (XTI/MCLK), Q3.2
unnamed: C23.2, IC6.26 (XTO), Q3.1
unnamed: IC2.53 (PC12/UART5_TX/I2S3_SD/USART3_CK), R1.1
unnamed: IC2.51 (PC10/SPI3_SCK/I2S3_SCK/UART4_TX), R5.1
NORMALIZATION_PROBE: IC2.39 (PC8); also elsewhere on the board
POSITION_CV: IC2.23 (PA7/SPI1_MOSI/ADC7/TIM3_CH2); also elsewhere on the board
RESET: IC2.7 (NRST), JP1.10, R6.1, SW3.B (S), SW3.B' (S1)
RX: IC2.43 (PA10/USART1_RX/TIM1_CH3), JP2.4
STRUM: IC2.16 (PA2/USART2_TX/ADC2/TIM2_CH3); also elsewhere on the board
SW_MODE: IC2.61 (PB8/TIM4_CH3/I2C1_SCL); also elsewhere on the board
SW_POLYPHONY: IC2.62 (PB9/SPI2_NSS/I2S2_WS/I2C1_SDA/TIM4_CH4); also elsewhere on the board
TX: IC2.42 (PA9/USART1_TX/TIM1_CH2), JP2.5
VBAT: IC2.1 (VBAT)
V_OCT_CV: IC2.15 (PA1/USART2_RTS/UART4_RX/ADC1/TIM2_CH2); also elsewhere on the board

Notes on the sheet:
cc-by-sa
Main processor
Serial / System Bootloader
v2.0 and higher
Émilie Gillet
emilie.o.gillet@gmail.com

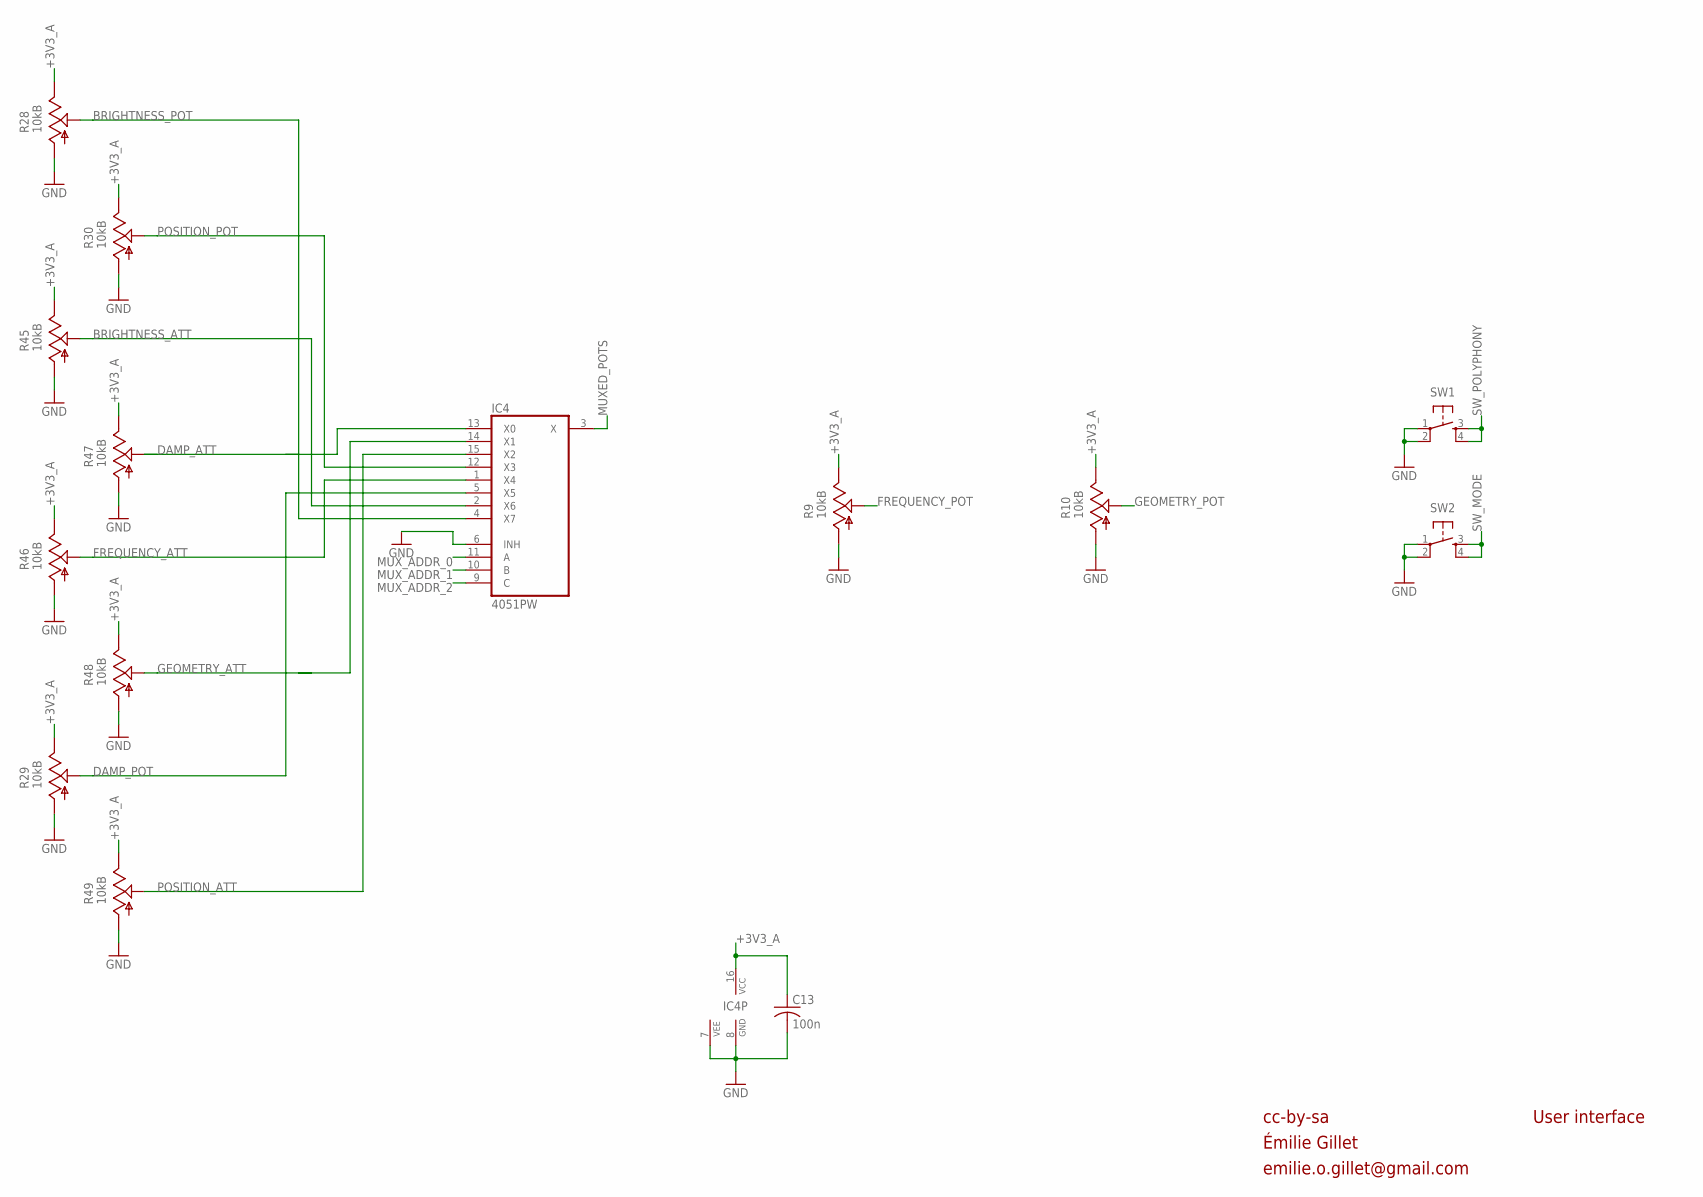
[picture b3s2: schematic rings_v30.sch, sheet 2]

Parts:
C13: 100n; C0603
IC4: 4051PW; TSSOP16
R9, R10, R28, R29, R30: 10kB; ALPS_POT_VERTICAL_PS
R45, R46, R47, R48, R49: 10kB; ALPS_POT_VERTICAL
SW1, SW2: TAC_SWITCHPTH; TACTILE-PTH

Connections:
+3V3_A: C13.1, IC4.16 (VCC), R9.P$1 (E), R10.P$1 (E), R28.P$1 (E), R29.P$1 (E), R30.P$1 (E), R45.P$1 (E), R46.P$1 (E), R47.P$1 (E), R48.P$1 (E), R49.P$1 (E); also elsewhere on the board
BRIGHTNESS_ATT: IC4.2 (X6), R45.P$2 (S)
BRIGHTNESS_POT: IC4.4 (X7), R28.P$2 (S)
DAMP_ATT: IC4.13 (X0), R47.P$2 (S)
DAMP_POT: IC4.5 (X5), R29.P$2 (S)
FREQUENCY_ATT: IC4.1 (X4), R46.P$2 (S)
FREQUENCY_POT: R9.P$2 (S); also elsewhere on the board
GEOMETRY_ATT: IC4.14 (X1), R48.P$2 (S)
GEOMETRY_POT: R10.P$2 (S); also elsewhere on the board
GND: C13.2, IC4.6 (INH), IC4.7 (VEE), IC4.8 (GND), R9.P$3 (A), R10.P$3 (A), R28.P$3 (A), R29.P$3 (A), R30.P$3 (A), R45.P$3 (A), R46.P$3 (A), R47.P$3 (A), R48.P$3 (A), R49.P$3 (A), SW1.1, SW1.2, SW2.1, SW2.2; also elsewhere on the board
MUXED_POTS: IC4.3 (X); also elsewhere on the board
MUX_ADDR_0: IC4.11 (A); also elsewhere on the board
MUX_ADDR_1: IC4.10 (B); also elsewhere on the board
MUX_ADDR_2: IC4.9 (C); also elsewhere on the board
POSITION_ATT: IC4.15 (X2), R49.P$2 (S)
POSITION_POT: IC4.12 (X3), R30.P$2 (S)
SW_MODE: SW2.3, SW2.4; also elsewhere on the board
SW_POLYPHONY: SW1.3, SW1.4; also elsewhere on the board

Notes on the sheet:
cc-by-sa
User interface
Émilie Gillet
emilie.o.gillet@gmail.com

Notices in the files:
rings/hardware_design/pcb/rings_v30.brd:
cc-by-sa Émilie Gillet, 2015. v3
